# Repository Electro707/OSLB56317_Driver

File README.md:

# OSLB56317-XX LED Driver

This project is to drive the OSLB56317 16x16 LED matrix I got from my trip to Japan (from [Akizuki](https://maps.app.goo.gl/3vW3UY29P5pvr1BS6))

# Project Structure
- `CAD`: FreeCAD Source file for enclosure
- `Firmware_Demo`: A quick demo firmware to get the display up and running
- `Firmware_FFT`: Firmware to display an audio spectrograph from a USB host
    - The firmware will act as a USB speaker, which audio must be routed to it
- `PCB`: KiCAD PCB source files

# Known Issues
- I goofed up on the RP2040's SPI wiring to the constant current led driver, so for now it is emulated in software
    - todo: make this a PIO block, or even a PIO block to drive the entire display?
- In the CAD file, there is no easy way to take it apart other than pushing a small flat head between the display and the case. With PLA, the case is maluable enough to bend
    - todo: add some small slot eventually to be able to easily remove the display assembly
- In the schematic, the columns and row new names should be swapped (don't ask how that happened), but this has no effects on functionality
- In `Firmware_FFT`, every now and then the main loop will unexpectantly stop, randomly
    - todo: attach debugger and see what causes this crash, probably some incorrect memory indexing
    
# todo, maybe
- [ ] Develop a PIO block for the LED matrix
- [ ] Create more fun demo codes (animation?)
- [x] Create a USB audio spectrum analyzer

# License
This project, except for the external [Firmware_FFT/Adafruit_ZeroFFT](Firmware_FFT/Adafruit_ZeroFFT), is licensed under GPLv3. See [LICENSE.md](LICENSE.md) for details.

# Credit
A fork of [Adafruit's ZeroFFT library, by donmccoy](https://github.com/donmccoy/Adafruit_ZeroFFT/tree/bugfix), was used in this project, and that is licensed under BSD-3

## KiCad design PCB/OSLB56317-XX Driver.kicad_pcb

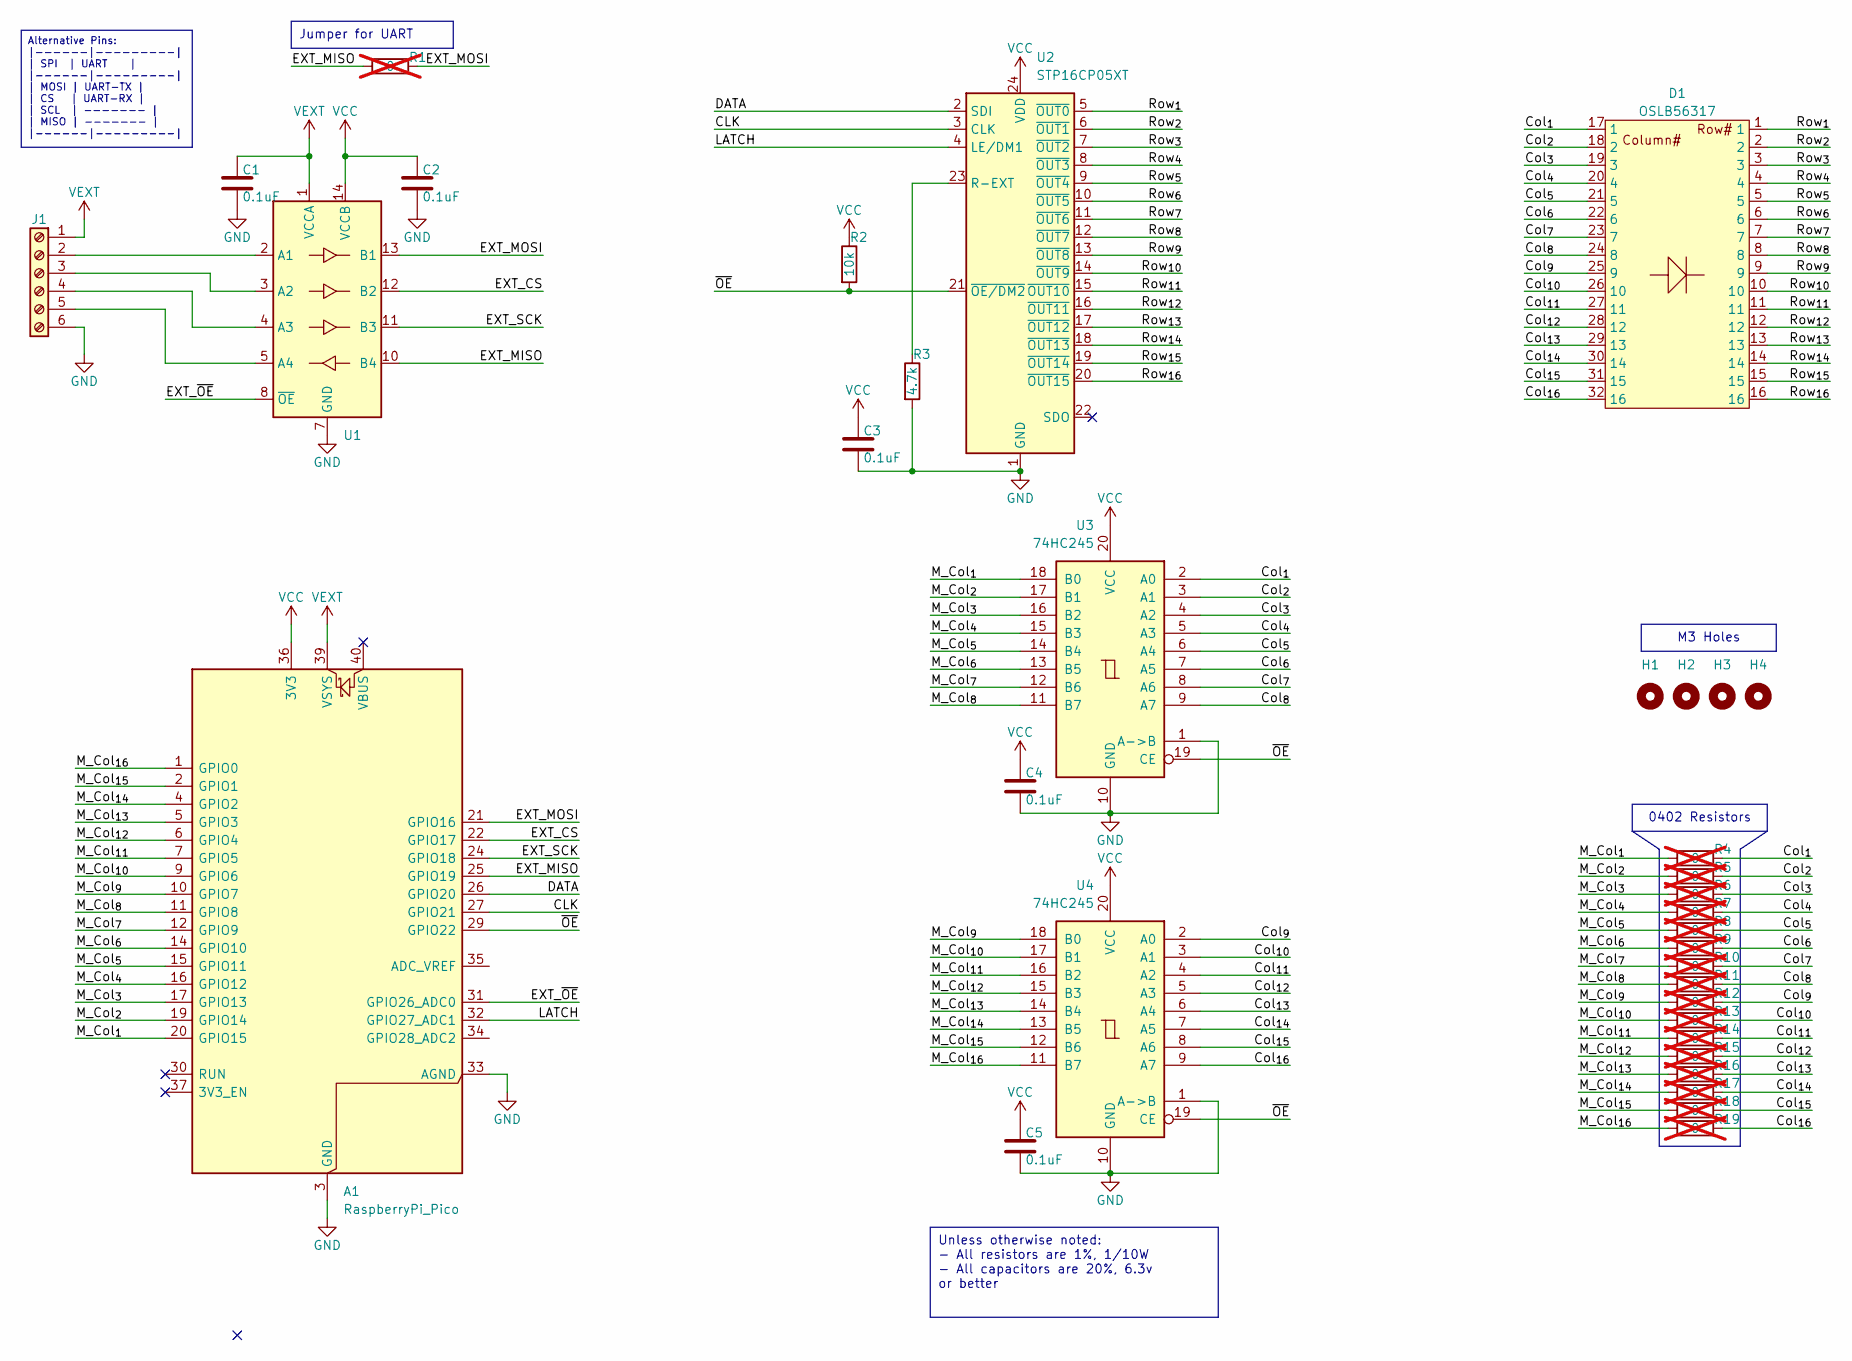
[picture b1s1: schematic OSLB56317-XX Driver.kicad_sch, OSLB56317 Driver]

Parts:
A1: RaspberryPi_Pico; RaspberryPi_Pico_Original_SMD_HandSolder
C1, C2, C3, C4, C5: 0.1uF; C_0805_2012Metric
D1: OSLB56317; OSLB56317-XX
H1, H2, H3, H4: MountingHole_Pad; MountingHole_3.2mm_M3
J1: Screw_Terminal_01x06; TerminalBlock_Phoenix_MPT-0,5-6-2.54_1x06_P2.54mm_Horizontal
R1, R4, R5, R6, R7, R8, R9, R10, R11, R12, R13, R14, R15, R16, R17, R18, R19: 0; R_0402_1005Metric; not fitted
R2: 10k; R_0805_2012Metric
R3: 4.7k; R_0805_2012Metric
U1: TSSOP-14_4.4x5mm_P0.65mm
U2: STP16CP05XT; HTSSOP-24-1EP_4.4x7.8mm_P0.65mm_EP3.2x5mm
U3, U4: 74HC245; TSSOP-20_4.4x6.5mm_P0.65mm

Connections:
/CLK: A1.27 (GPIO21), U2.3 (CLK)
/Col_{1}: D1.17 (1), R4.2, U3.2 (A0)
/Col_{2}: D1.18 (2), R5.2, U3.3 (A1)
/Col_{3}: D1.19 (3), R6.2, U3.4 (A2)
/Col_{4}: D1.20 (4), R7.2, U3.5 (A3)
/Col_{5}: D1.21 (5), R8.2, U3.6 (A4)
/Col_{6}: D1.22 (6), R9.2, U3.7 (A5)
/Col_{7}: D1.23 (7), R10.2, U3.8 (A6)
/Col_{8}: D1.24 (8), R11.2, U3.9 (A7)
/Col_{9}: D1.25 (9), R12.2, U4.2 (A0)
/Col_{10}: D1.26 (10), R13.2, U4.3 (A1)
/Col_{11}: D1.27 (11), R14.2, U4.4 (A2)
/Col_{12}: D1.28 (12), R15.2, U4.5 (A3)
/Col_{13}: D1.29 (13), R16.2, U4.6 (A4)
/Col_{14}: D1.30 (14), R17.2, U4.7 (A5)
/Col_{15}: D1.31 (15), R18.2, U4.8 (A6)
/Col_{16}: D1.32 (16), R19.2, U4.9 (A7)
/DATA: A1.26 (GPIO20), U2.2 (SDI)
/EXT_CS: A1.22 (GPIO17), U1.12 (B2)
/EXT_MISO: A1.25 (GPIO19), R1.1, U1.10 (B4)
/EXT_MOSI: A1.21 (GPIO16), R1.2, U1.13 (B1)
/EXT_SCK: A1.24 (GPIO18), U1.11 (B3)
/EXT_~OE: A1.31 (GPIO26_ADC0), U1.8 (~OE)
/LATCH: A1.32 (GPIO27_ADC1), U2.4 (LE/DM1)
/M_Col_{1}: A1.20 (GPIO15), R4.1, U3.18 (B0)
/M_Col_{2}: A1.19 (GPIO14), R5.1, U3.17 (B1)
/M_Col_{3}: A1.17 (GPIO13), R6.1, U3.16 (B2)
/M_Col_{4}: A1.16 (GPIO12), R7.1, U3.15 (B3)
/M_Col_{5}: A1.15 (GPIO11), R8.1, U3.14 (B4)
/M_Col_{6}: A1.14 (GPIO10), R9.1, U3.13 (B5)
/M_Col_{7}: A1.12 (GPIO9), R10.1, U3.12 (B6)
/M_Col_{8}: A1.11 (GPIO8), R11.1, U3.11 (B7)
/M_Col_{9}: A1.10 (GPIO7), R12.1, U4.18 (B0)
/M_Col_{10}: A1.9 (GPIO6), R13.1, U4.17 (B1)
/M_Col_{11}: A1.7 (GPIO5), R14.1, U4.16 (B2)
/M_Col_{12}: A1.6 (GPIO4), R15.1, U4.15 (B3)
/M_Col_{13}: A1.5 (GPIO3), R16.1, U4.14 (B4)
/M_Col_{14}: A1.4 (GPIO2), R17.1, U4.13 (B5)
/M_Col_{15}: A1.2 (GPIO1), R18.1, U4.12 (B6)
/M_Col_{16}: A1.1 (GPIO0), R19.1, U4.11 (B7)
/Row_{1}: D1.1, U2.5 (~OUT0)
/Row_{2}: D1.2, U2.6 (~OUT1)
/Row_{3}: D1.3, U2.7 (~OUT2)
/Row_{4}: D1.4, U2.8 (~OUT3)
/Row_{5}: D1.5, U2.9 (~OUT4)
/Row_{6}: D1.6, U2.10 (~OUT5)
/Row_{7}: D1.7, U2.11 (~OUT6)
/Row_{8}: D1.8, U2.12 (~OUT7)
/Row_{9}: D1.9, U2.13 (~OUT8)
/Row_{10}: D1.10, U2.14 (~OUT9)
/Row_{11}: D1.11, U2.15 (~OUT10)
/Row_{12}: D1.12, U2.16 (~OUT11)
/Row_{13}: D1.13, U2.17 (~OUT12)
/Row_{14}: D1.14, U2.18 (~OUT13)
/Row_{15}: D1.15, U2.19 (~OUT14)
/Row_{16}: D1.16, U2.20 (~OUT15)
/~OE: A1.29 (GPIO22), R2.2, U2.21 (~OE/DM2), U3.19 (CE), U4.19 (CE)
GND: A1.3 (GND), A1.8 (GND), A1.13 (GND), A1.18 (GND), A1.23 (GND), A1.28 (GND), A1.33 (AGND), A1.38 (GND), C1.2, C2.2, C3.2, C4.2, C5.2, J1.6, R3.2, U1.7 (GND), U2.1 (GND), U2.25 (GND), U3.1 (A->B), U3.10 (GND), U4.1 (A->B), U4.10 (GND)
unnamed: J1.2, U1.2 (A1)
unnamed: J1.3, U1.3 (A2)
unnamed: J1.4, U1.4 (A3)
unnamed: J1.5, U1.5 (A4)
unnamed: R3.1, U2.23 (R-EXT)
VCC: A1.36 (3V3), C2.1, C3.1, C4.1, C5.1, R2.1, U1.14 (VCCB), U2.24 (VDD), U3.20 (VCC), U4.20 (VCC)
VEXT: A1.39 (VSYS), C1.1, J1.1, U1.1 (VCCA)

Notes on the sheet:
M3 Holes
Alternative Pins: |------|---------| | SPI | UART | |------|---------| | MOSI | UART-TX | | CS | UART-RX | | SCL | ------- | | MISO | ------- | |------|---------|
Unless otherwise noted: - All resistors are 1%, 1/10W - All capacitors are 20%, 6.3v or better
0402 Resistors
Jumper for UART

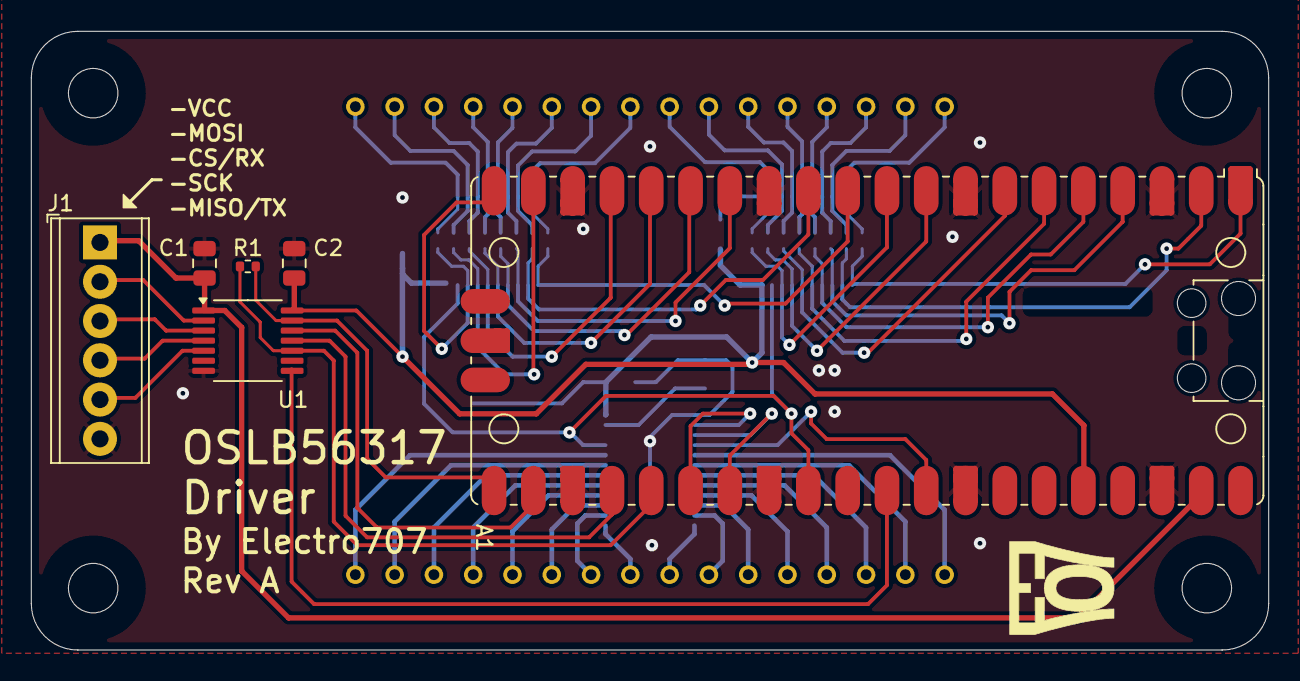
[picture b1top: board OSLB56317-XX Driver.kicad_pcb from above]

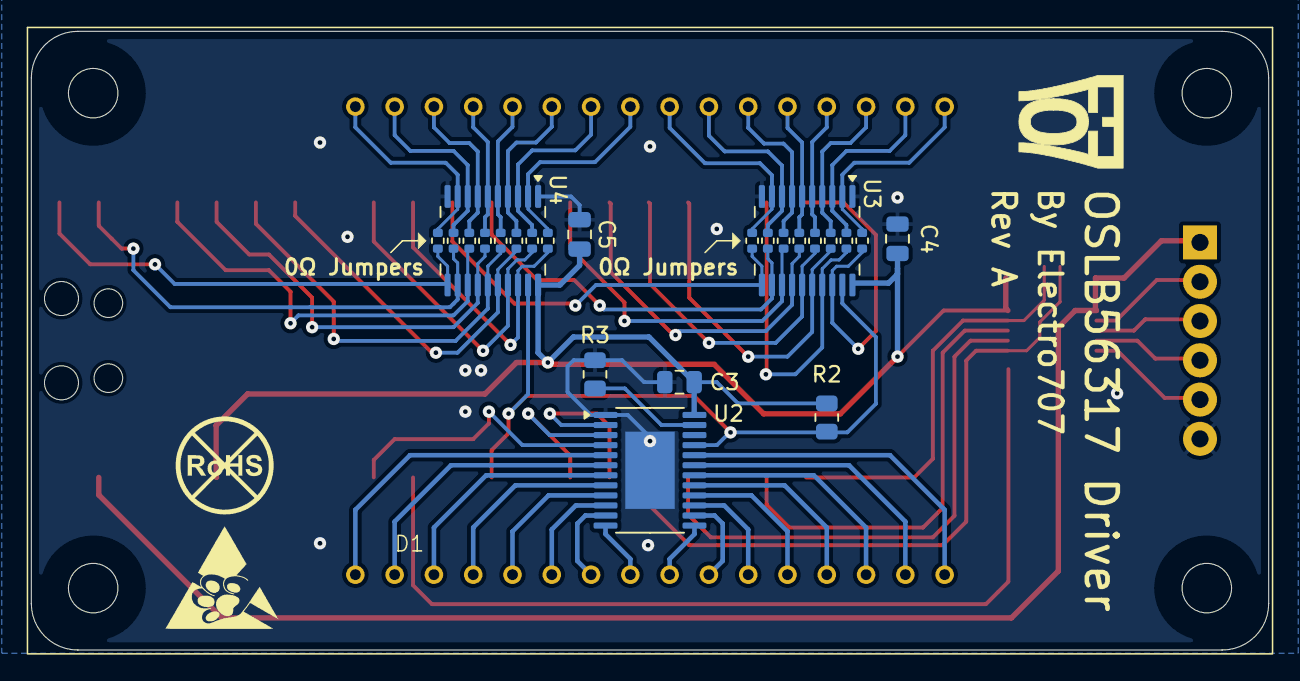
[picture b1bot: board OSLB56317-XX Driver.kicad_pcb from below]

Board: 2 copper layers, 80.0 x 40.0 mm, 35 parts (25 on the bottom side), 65 nets.

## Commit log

2024-12-10 Initial Release
2024-12-25 Added some CAD files
2024-12-25 Added CAD file note in readme
2025-01-01 Added firmware for a spectrograph over USB
2025-01-01 Added bug now in README
2025-01-01 Refractored firmware, much needed change
2025-01-01 Added project structure to README. Moved a variable to define.h
